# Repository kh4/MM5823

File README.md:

MM5823
======

MM5823N drop in replacement module (2xHEF4520)

These boards are meant to help replacing MM5823N vintage IC with more common alternatives.

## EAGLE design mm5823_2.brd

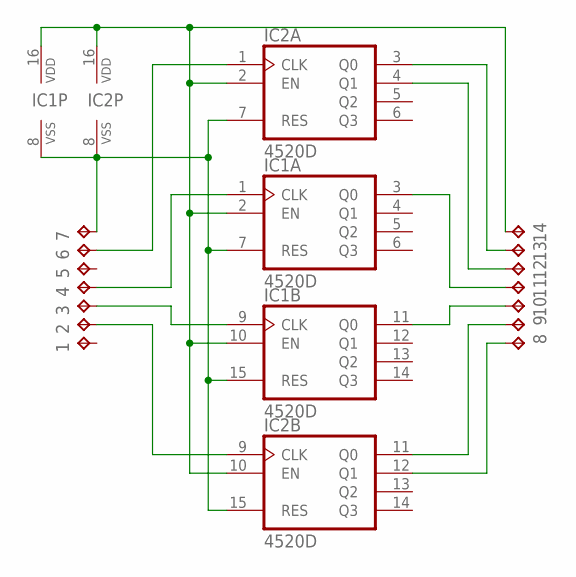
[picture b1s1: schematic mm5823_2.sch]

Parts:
1, 2, 3, 4, 5, 6, 7, 8, 9, 10, 11, 12, 13, 14: TPB1,27; B1,27
IC1, IC2: 4520D; SO16

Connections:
unnamed: 13.TP, IC2.3 (Q0)
unnamed: 12.TP, IC2.4 (Q1)
unnamed: 8.TP, IC2.12 (Q1)
unnamed: 9.TP, IC2.11 (Q0)
unnamed: 6.TP, IC2.1 (CLK)
unnamed: 2.TP, IC2.9 (CLK)
unnamed: 11.TP, IC1.3 (Q0)
unnamed: 10.TP, IC1.11 (Q0)
unnamed: 4.TP, IC1.1 (CLK)
unnamed: 3.TP, IC1.9 (CLK)
unnamed: 7.TP, IC1.7 (RES), IC1.8 (VSS), IC1.15 (RES), IC2.7 (RES), IC2.8 (VSS), IC2.15 (RES)
unnamed: 14.TP, IC1.2 (EN), IC1.10 (EN), IC1.16 (VDD), IC2.2 (EN), IC2.10 (EN), IC2.16 (VDD)

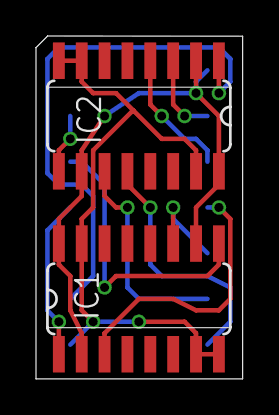
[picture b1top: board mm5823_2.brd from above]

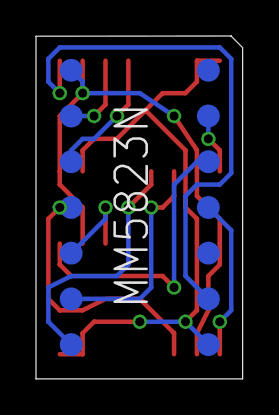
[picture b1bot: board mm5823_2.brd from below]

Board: 2 copper layers, 11.5 x 19.1 mm, 16 parts (14 on the bottom side), 12 nets.

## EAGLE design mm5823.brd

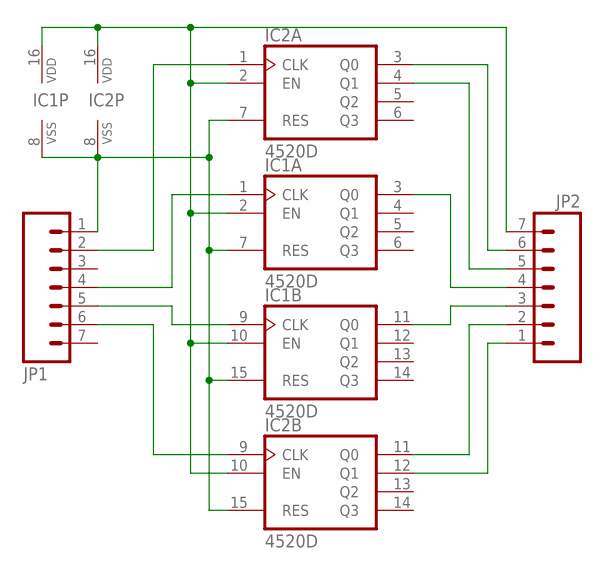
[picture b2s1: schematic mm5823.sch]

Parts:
IC1, IC2: 4520D; SO16
JP1, JP2: M07; 1X07

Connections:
unnamed: IC2.3 (Q0), JP2.6
unnamed: IC2.4 (Q1), JP2.5
unnamed: IC2.12 (Q1), JP2.1
unnamed: IC2.11 (Q0), JP2.2
unnamed: IC2.1 (CLK), JP1.2
unnamed: IC2.9 (CLK), JP1.6
unnamed: IC1.3 (Q0), JP2.4
unnamed: IC1.11 (Q0), JP2.3
unnamed: IC1.1 (CLK), JP1.4
unnamed: IC1.9 (CLK), JP1.5
unnamed: IC1.7 (RES), IC1.8 (VSS), IC1.15 (RES), IC2.7 (RES), IC2.8 (VSS), IC2.15 (RES), JP1.1
unnamed: IC1.2 (EN), IC1.10 (EN), IC1.16 (VDD), IC2.2 (EN), IC2.10 (EN), IC2.16 (VDD), JP2.7

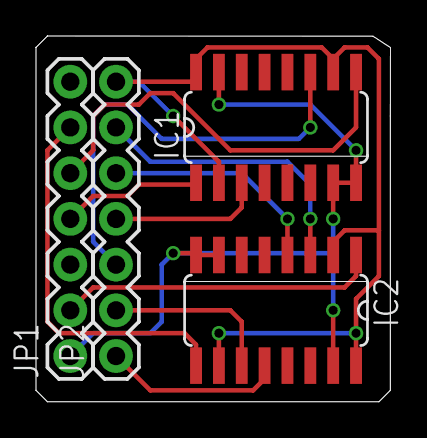
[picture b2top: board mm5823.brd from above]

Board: 2 copper layers, 19.7 x 20.3 mm, 4 parts (0 on the bottom side), 12 nets.

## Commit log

2014-09-13 Initial versions: MM5823 - edgemounted version MM5823_2 - flat minimal board

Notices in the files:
parts and their libraries:
SparkFun-Connectors: Licensing: CC v3.0 Share-Alike You are welcome to use this library for commercial purposes.
